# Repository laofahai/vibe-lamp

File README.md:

**English** | [简体中文](README.zh-CN.md)

# Vibe Lamp

Physical ambient status light for AI coding agents.

Vibe Lamp turns local coding-agent state into desk light: blue when the agent is working, green when it finishes, red when it needs you, and amber when the connection is lost.

Core V1 is a complete ESP32-C3 controller board with USB-C power/programming, a board-mounted WS2812B status LED, a reset/provisioning button, and a reserved WS2812 expansion pad. The KiCad source, 3D renders, Gerber, BOM, and CPL files are included.

Inspired by [Vibe Island](https://vibeisland.app/), but independent from it. Vibe Lamp consumes agent hooks directly and can coexist with other hook consumers.

---

## Agent Support

| Level | Agents / tools | How it works |
|---|---|---|
| Built in | Claude Code, Codex | `daemon/install.py` installs local hooks and launchd autostart on macOS. |
| Generic API | OpenCode, Qwen Code, Gemini CLI, Aider, Cursor, Windsurf, CodeBuddy / WorkBuddy, Trae, MarsCode / Doubao, Factory / Droid-style tools | Any tool that can run a hook, plugin, wrapper, or notification command can POST normalized events to `/event/generic`. |
| Future adapters | Tool-specific integrations | Add adapter logic in the Mac daemon only; the ESP32 firmware stays agent-agnostic. |

Generic event example:

```bash
curl -s -o /dev/null --max-time 1 \
  -X POST http://127.0.0.1:8787/event/generic \
  -H 'Content-Type: application/json' \
  -d '{"agent":"opencode","session_id":"default","state":"working","tool":"code"}' || true
```

Supported normalized states are `idle`, `working`, `done`, `error`, and `needs_you`. See [daemon/AGENTS.md](daemon/AGENTS.md) for adapter notes.

---

## Architecture

All decision-making lives on the Mac. The ESP32 is a display endpoint.

```
Claude Code / Codex / generic agent
        │
        ▼
Mac daemon
  - normalizes hook events
  - merges multiple sessions
  - pushes state + heartbeat
        │ WiFi / HTTP
        ▼
ESP32 firmware
  - renders LED color/animation
  - enters lost state when heartbeat stops
```

Merge priority for a single LED:

```text
needs_you > error > working > done > idle
```

The lamp never freezes on stale state: if the daemon or network disappears, firmware switches to amber lost mode after the watchdog timeout.

---

## Hardware

Two hardware paths are supported:

| Path | Use it for | Notes |
|---|---|---|
| Core V1 PCBA | Finished build | Recommended. Factory-assembled ESP32-C3 board with board-mounted WS2812B. |
| Breadboard prototype | Bring-up and experiments | ESP32 dev board plus RGB LED or WS2812 ring. |

Core V1 production files live in [hardware/kicad/vibe_lamp_core_v1](hardware/kicad/vibe_lamp_core_v1):

- KiCad PCB source
- PCB renders
- JLCPCB Gerber zip
- JLCPCB BOM and CPL

<details>
<summary>Breadboard prototype parts</summary>

RGB LED prototype:

| Part | Qty | Notes |
|---|---:|---|
| ESP32 dev board | 1 | Any `esp32dev`-compatible board |
| Common-cathode RGB LED | 1 | 4-pin LED |
| 220 ohm resistor | 3 | One per R/G/B channel |
| Breadboard | 1 | Bring-up |
| Jumper wires | Several | Board-dependent |
| USB data cable | 1 | Power and flashing |

WS2812 ring prototype:

| Part | Qty | Notes |
|---|---:|---|
| ESP32 dev board | 1 | Same firmware stack |
| WS2812 / WS2812B ring | 1 | 16 LEDs by default |
| 330 ohm resistor | 1 | In series with DIN |
| 1000 uF electrolytic capacitor | 1 | Across 5V and GND |
| Jumper wires + USB data cable | Several | Power, data, flashing |

</details>

Detailed wiring, flashing, WiFi provisioning, and self-test steps are in [HARDWARE.md](HARDWARE.md).

---

## Quick Start

```bash
# Core V1 firmware
cd firmware
pio run -e c3_core_v1 -t upload

# Mac daemon + Claude Code / Codex hooks
cd ../daemon
python install.py install
```

After WiFi provisioning, test the lamp directly:

```bash
curl --noproxy '*' -X POST http://vibelamp-<id>.local/state \
  -H 'Content-Type: application/json' \
  -d '{"sessions":[{"state":"working","tool":"code"}]}'
```

---

## Development

```bash
# Daemon tests
cd daemon
python -m pytest

# Firmware logic tests
cd ../firmware
pio test -e native

# Firmware builds
pio run -e c3_core_v1
pio run -e esp32
pio run -e esp32_ring
```

The `pio` command can use the repo virtualenv: `.venv/bin/pio`.

---

## Status

Done:

- ESP32 firmware: WiFi provisioning, HTTP state API, mDNS, watchdog lost mode, RGB/WS2812 display drivers, animations, multi-session rendering.
- macOS daemon: Claude Code and Codex hooks, generic event API, session merge, heartbeat, retry, rediscovery, launchd autostart.
- Core V1 hardware: KiCad board source, renders, JLCPCB Gerber/BOM/CPL.

Planned:

- Dedicated adapters for more coding agents.
- OTA firmware update.
- Phone control page.
- Enclosure and diffuser polish.
- BLE fallback when WiFi is unavailable.

---

## Repository Layout

```text
vibe-lamp/
├── hardware/    # Core V1 docs, KiCad source, renders, fab outputs
├── firmware/    # ESP32 firmware, PlatformIO environments, native tests
├── daemon/      # macOS daemon, hook installer, normalization logic, pytest
└── scripts/     # release packaging helpers
```

---

## License

MIT. See [LICENSE](LICENSE).

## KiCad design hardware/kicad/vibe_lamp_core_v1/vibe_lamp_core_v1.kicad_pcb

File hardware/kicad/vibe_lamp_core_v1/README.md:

# Vibe Lamp Core V1 (KiCad)

Core V1 桌面状态灯主控板的 KiCad 工程目录。当前版本已经包含 PCB 源文件、渲染图、JLCPCB Gerber/BOM/CPL 输出，可作为 PCBA 打样下单基础。

40×40mm 圆角方板 · 2 层 · ESP32-C3-MINI-1（自带 PCB 天线，天线 keep-out 在位）· USB-C 供电+原生 USB · 板载 3.3V LDO · 板载 WS2812B 状态灯 · WS2812 扩展焊盘 · 清网按钮 · 工厂贴片，用户不焊接主板。

## 当前状态

- 电气完整：0 短路、0 未连接。
- 生产资料已生成：`fab/vibe_lamp_core_v1-gerber.zip`、`fab/vibe_lamp_core_v1-bom.csv`、`fab/vibe_lamp_core_v1-cpl.csv`。
- 3D 预览图在 `renders/`。
- 详细布线/DRC 说明见 `../../v1_routing_status.md`。

## 目录内容

| 路径 | 用途 |
|---|---|
| `vibe_lamp_core_v1.kicad_pcb` | PCB 源文件 |
| `vibe_lamp_core_v1.kicad_pro` | KiCad 工程配置 |
| `libs/` | 本工程使用的符号、封装、3D 模型 |
| `scripts/` | 生成/布线/导出辅助脚本 |
| `renders/` | 顶视与等轴测 3D 渲染图 |
| `fab/` | JLCPCB 下单文件 |

## 下单入口

1. 先读 `../../v1_routing_status.md`，确认剩余 DRC 告警的性质。
2. JLCPCB 下单时上传 `fab/vibe_lamp_core_v1-gerber.zip`。
3. 选择 PCBA 后上传 `fab/vibe_lamp_core_v1-bom.csv` 与 `fab/vibe_lamp_core_v1-cpl.csv`。
4. 被动件按阻值/容值在 JLCPCB 页面确认基础库匹配。

## 注意
- 天线 keep-out 是本板第一约束：模组天线端贴板边，该区域两层禁铜/禁走线/禁过孔/禁器件。
- 下单/编辑前留意 KiCad 自动回写 `.kicad_pro` 的问题，详见 `../../v1_routing_status.md`。

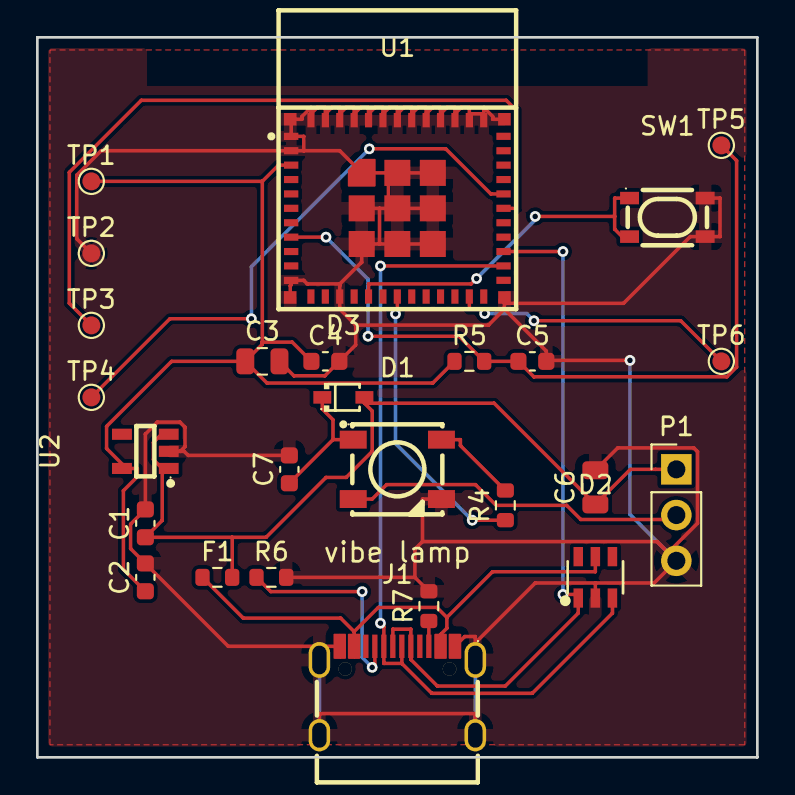
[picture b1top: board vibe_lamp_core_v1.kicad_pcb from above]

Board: 2 copper layers, 40.0 x 40.0 mm, 26 parts (0 on the bottom side), 17 nets.

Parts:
C1, C2: 1uF; C_0603_1608Metric
C3: 10uF; C_0805_2012Metric
C4, C5, C7: 100nF; C_0603_1608Metric
C6: 470uF; C_0805_2012Metric
D1: WS2812B; LED-SMD_4P-L5.0-W5.0-TL_WS2812B-B
D2: USBLC6-2SC6; SOT-23-6_L2.9-W1.6-P0.95-LS2.8-BL
D3: 1N4148WS; SOD-323_L1.8-W1.3-LS2.5-RD
F1: 0R; R_0603_1608Metric
J1: USB-C-TYPE-C-31-M-12; USB-C_SMD-TYPE-C-31-M-12_1
P1: WS2812-EXT-1x3; PinHeader_1x03_P2.54mm_Vertical
R4: 330; R_0603_1608Metric
R5: 10k; R_0603_1608Metric
R6, R7: 5.1k; R_0603_1608Metric
SW1: SW-PUSH; KEY-SMD_4P-L4.2-W3.2-P2.20-LS4.6
TP1, TP2, TP3, TP4, TP5, TP6: TestPoint_Pad_D1.0mm
U1: ESP32-C3-MINI-1; WIFIM-SMD_ESP32-C3-MINI-1
U2: AP2112K-3.3; SOT-25-5_L2.9-W1.6-P0.95-LS2.8-BL

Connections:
+3V3: C2.1, C3.1, C4.1, R5.1, TP1.1, U1.3, U2.5
+5V: C1.1, C6.1, D3.2, F1.2, P1.1, U2.1, U2.3
BTN: SW1.1, SW1.3, U1.16
CC1: J1.A5, R6.1
CC2: J1.B5, R7.1
EN: C5.1, R5.2, TP5.1, U1.8
GND: C1.2, C2.2, C3.2, C4.2, C5.2, C6.2, C7.2, D1.3, D2.2, J1.1, J1.2, J1.3, J1.4, J1.A1B12, J1.B1A12, P1.3, R6.2, R7.2, SW1.2, SW1.4, TP2.1, U1.1, U1.2, U1.11, U1.14, U1.36, U1.37, U1.38, U1.39, U1.40, U1.41, U1.42, U1.43, U1.44, U1.45, U1.46, U1.47, U1.48, U1.49, U1.50, U1.51, U1.52, U1.53, U2.2
IO4: R4.1, U1.18
IO9: TP6.1, U1.23
LED5V: C7.1, D1.1, D3.1
UART_RX: TP3.1, U1.30
UART_TX: TP4.1, U1.31
USB_DM: D2.3, J1.A7, J1.B7, U1.26
USB_DP: D2.1, J1.A6, J1.B6, U1.27
VBUS: D2.5, F1.1, J1.A4B9, J1.B4A9
WS_DIN: D1.4, R4.2
WS_DOUT: D1.2, P1.2

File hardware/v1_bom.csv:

位号,数量,器件,规格,封装,装配方式,立创料号,备注
U1,1,无线主控模组,ESP32-C3-MINI-1,模组贴片,工厂贴片,C2934569,乐鑫原厂;自带PCB天线无需外置天线
J1,1,USB-C 母座,USB2.0 供电+数据,TYPE-C-31-M-12,工厂贴片,C165948,16脚立创常用可贴片款
U2,1,3.3V 稳压,AP2112K-3.3 (>=500mA),SOT-25-5,工厂贴片,C51118,主控3.3V供电
D1,1,数字RGB灯,WS2812B (单线/24位色),SMD5050-4P,工厂贴片,C2761795,板载灯;脚序VDD/DOUT/VSS/DIN;库存55万
D2,1,USB ESD 保护,USBLC6-2SC6,SOT-23-6,工厂贴片,C7519,D+/D-/VBUS TVS;原型可贴可不贴
D3,1,WS2812 电平保障二极管,1N4148WS,SOD-323,工厂贴片,C2128,5V串压降~0.7V给D1供电(LED5V~4.3V),使3.3V数据达标;基础库
R4,1,WS2812 数据串联电阻,330 欧姆,0603,工厂贴片,,GPIO4→R4→D1.DIN
R5,1,使能脚上拉,10k,0603,工厂贴片,,EN 上拉到 3.3V
R6,1,USB-C CC1 下拉,5.1k,0603,工厂贴片,,CC1 到地
R7,1,USB-C CC2 下拉,5.1k,0603,工厂贴片,,CC2 到地
F1,1,VBUS 输入保护,0Ω 跳线(可换PTC),0603,工厂贴片,,缺省0Ω;需过流保护改自恢复保险丝
C1,1,稳压输入电容,1uF,0603,工厂贴片,,LDO 输入
C2,1,稳压输出电容,1uF,0603,工厂贴片,,LDO 输出
C3,1,主控储能电容,10uF,0805,工厂贴片,,靠近主控3.3V
C4,1,主控去耦,100nF,0603,工厂贴片,,靠近主控3.3V
C5,1,EN 电容,100nF,0603,工厂贴片,,上电复位稳定
C7,1,D1 电源去耦,100nF,0603,工厂贴片,,靠近 WS2812B 电源
SW1,1,清网按钮,SKRPABE010 轻触开关,SMD 4.2x3.2,工厂贴片,C115360,接GPIO10;左侧两脚一端子
C6,1,灯带储能电容,470uF >=6.3V,0805/钽,默认不贴(DNP),,仅外接灯带时需要
P1,1,灯带扩展口,5V/数据/地,1x3 2.54排针,默认不贴(DNP),,WS2812 级联口;D1.DOUT→P1
TP1,1,测试焊盘,3.3V,焊盘,不贴件,,调试用
TP2,1,测试焊盘,地,焊盘,不贴件,,调试用
TP3,1,测试焊盘,UART RXD0,焊盘,不贴件,,调试/串口
TP4,1,测试焊盘,UART TXD0,焊盘,不贴件,,调试/串口
TP5,1,测试焊盘,EN,焊盘,不贴件,,调试用
TP6,1,测试焊盘,IO9(下载),焊盘,不贴件,,进下载模式
被动件说明,,,,,,,"R/C/0Ω 在 JLCPCB 下单界面按值+0603封装自动匹配基础库,无需预填料号"

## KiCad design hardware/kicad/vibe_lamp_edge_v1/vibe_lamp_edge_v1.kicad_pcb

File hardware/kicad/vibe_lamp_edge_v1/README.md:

# Vibe Lamp Edge V1 PCB Draft

This is a first KiCad PCB draft for the magnetic MacBook A-cover lamp form factor.
It is a mechanical/electrical placement sketch, not a fabrication-ready routed PCB.

## Mechanical Direction

- PCB outline: 38 mm x 16 mm rectangle.
- PCB stackup: FR4, 2 layers, 1 oz copper, 1.6 mm thickness.
- Minimum rule target: 6 mil track/clearance, 0.3 mm drill.
- USB-C sits on the bottom edge.
- Four edge-facing RGB/NeoPixel LED positions sit near the top edge.
- Back-side center area is reserved for a thin magnet or magnetic sheet in the enclosure.
- ESP32-C3 antenna end is placed near the top edge with a keepout note.

## Manufacturing Notes

- Solder mask: choose black or white for a product look; green is fine for engineering samples.
- Silkscreen: white.
- Surface finish: HASL is acceptable, ENIG is nicer for small pads and appearance.
- This file is a layout/concept draft. Replace placeholder footprints with exact supplier parts before ordering.
- Do not export Gerbers from this draft for fabrication yet. Nets and footprints are placeholders and routing is intentionally not complete.

## Open Items Before Fabrication

- Select exact USB-C receptacle footprint.
- Select exact LED package: 2020/2427 side-view addressable RGB, or discrete RGB LEDs.
- Decide whether V1 uses one RGB LED from the existing firmware or a WS2812 chain.
- Run KiCad DRC after footprints and schematic nets are finalized.
- Verify enclosure wall thickness, diffuser geometry, and magnet placement.

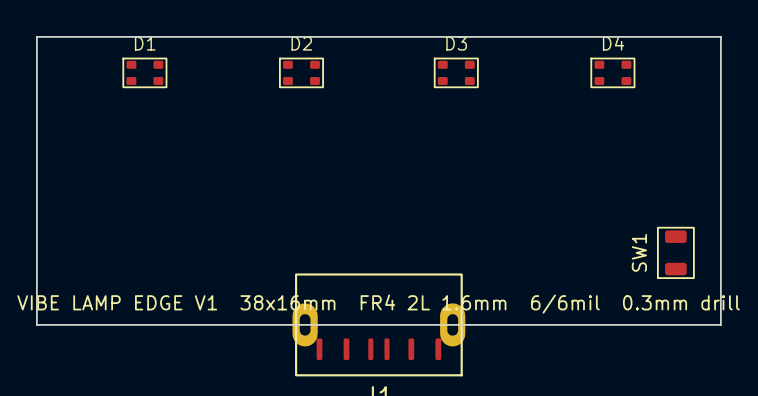
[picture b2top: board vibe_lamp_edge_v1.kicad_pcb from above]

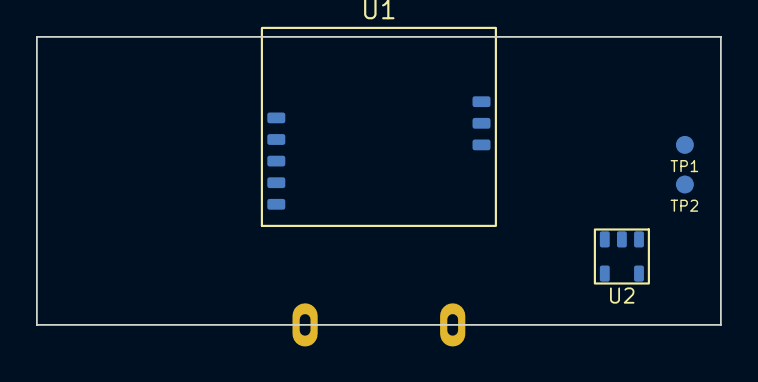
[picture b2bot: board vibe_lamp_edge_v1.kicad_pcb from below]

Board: 2 copper layers, 38.0 x 16.0 mm, 10 parts (4 on the bottom side), 10 nets, no tracks yet.

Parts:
D1, D2, D3, D4: RGB/NeoPixel edge LED; LED_RGB_2020_SideView_Placeholder
J1: USB-C USB2.0; USB-C_Receptacle_BottomEdge
SW1: Reset/Clear WiFi; SW_SPST_Placeholder
TP1: 3V3; TestPoint_Pad_D1.0mm
TP2: GND; TestPoint_Pad_D1.0mm
U1: ESP32-C3-MINI-1
U2: 3V3 LDO; SOT-23-5

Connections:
+3V3: TP1.1, U1.2, U2.3
+5V: D1.1, D2.1, D3.1, D4.1, J1.A4, J1.A9, U2.1
GND: D1.2, D2.2, D3.2, D4.2, J1.A1, J1.A12, J1.S1, J1.S2, SW1.2, TP2.1, U1.1, U1.8, U2.2
LED_D1_D2: D1.4, D2.3
LED_D2_D3: D2.4, D3.3
LED_D3_D4: D3.4, D4.3
LED_DIN: D1.3, U1.4
RESET_BTN: SW1.1, U1.5
USB_DN: J1.A7, U1.7
USB_DP: J1.A6, U1.6

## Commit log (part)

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2026-06-26 Release v0.2.0 OTA and device binding
2026-06-26 Fix CI pytest dependency
2026-06-26 Fix optional BLE bridge dependency in CI
2026-06-26 Split CI and release workflows
2026-06-27 Fix WiFi credential source of truth
2026-06-27 feat(daemon): add generic agent event endpoint
2026-06-30 docs: polish project readme and hardware docs
2026-06-30 docs: tighten readme and agent support
